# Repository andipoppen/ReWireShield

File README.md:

# ReWireShield
An Arduino compatible shield for rewiring D0-D13 and A0-A5

Exporting to SeedStudio format see:
http://support.seeedstudio.com/knowledgebase/articles/612798-export-pcb-gerber-from-cam

A gerber file viewer can be found here:
http://gerbv.geda-project.org/

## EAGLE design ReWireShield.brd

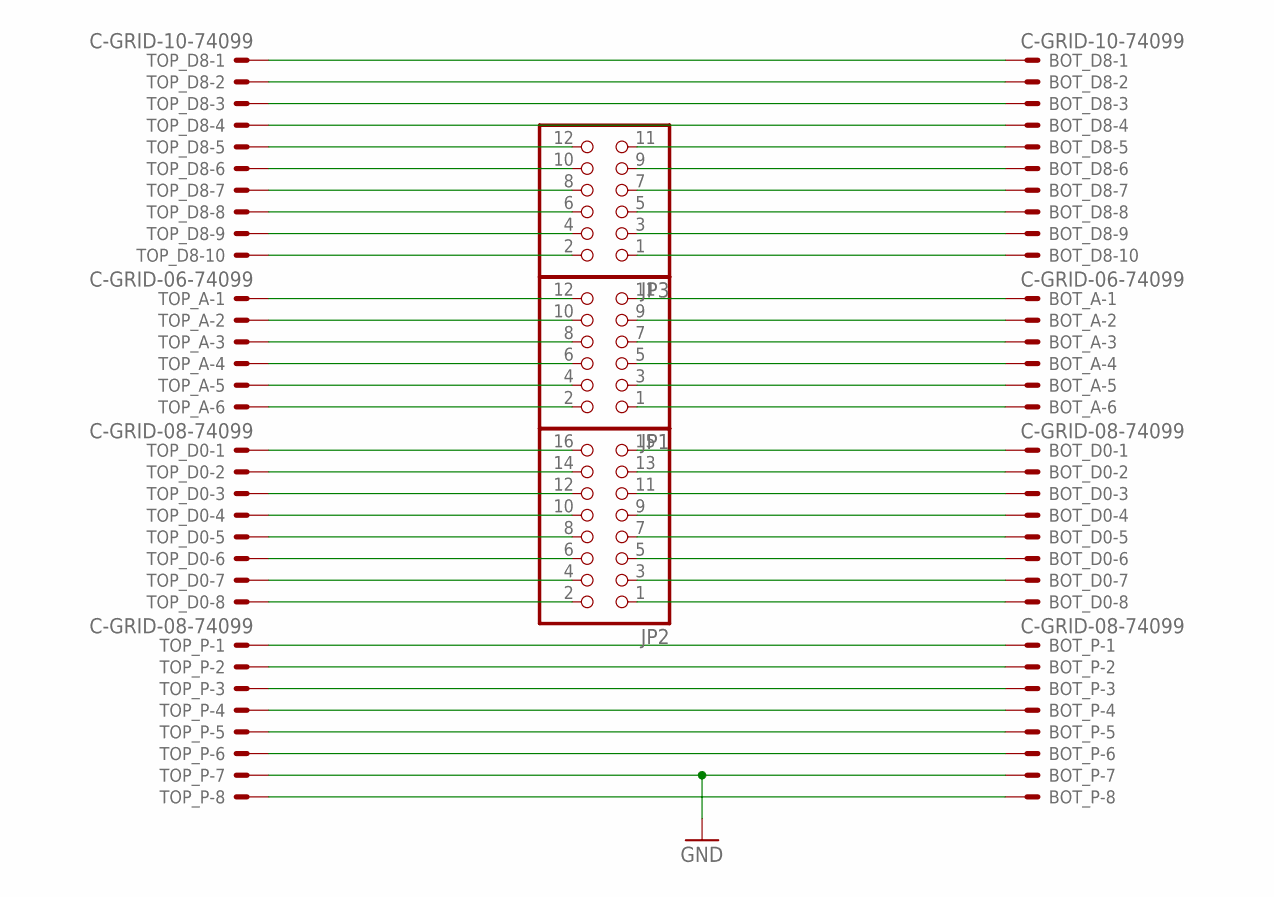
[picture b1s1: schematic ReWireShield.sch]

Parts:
BOT_A: C-GRID-06-74099; 74099-06
BOT_D0: C-GRID-08-74099; 74099-08
BOT_D8: C-GRID-10-74099; 74099-10
BOT_P: C-GRID-08-74099; 74099-08
JP1, JP3: PINHD-2X6/90; 2X06/90
JP2: PINHD-2X8/90; 2X08/90
TOP_A: C-GRID-06-74099; 74099-06
TOP_D0: C-GRID-08-74099; 74099-08
TOP_D8: C-GRID-10-74099; 74099-10
TOP_P: C-GRID-08-74099; 74099-08

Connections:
GND: BOT_P.7, TOP_P.7
unnamed: BOT_P.8, TOP_P.8
unnamed: JP3.2, TOP_D8.10
unnamed: BOT_P.6, TOP_P.6
unnamed: JP3.4, TOP_D8.9
unnamed: BOT_P.4, TOP_P.4
unnamed: BOT_P.3, TOP_P.3
unnamed: BOT_P.2, TOP_P.2
unnamed: BOT_P.1, TOP_P.1
unnamed: JP3.6, TOP_D8.8
unnamed: JP3.8, TOP_D8.7
unnamed: JP3.10, TOP_D8.6
unnamed: JP3.12, TOP_D8.5
unnamed: BOT_D8.10, JP3.1
unnamed: BOT_D8.9, JP3.3
unnamed: JP2.16, TOP_D0.1
unnamed: JP2.14, TOP_D0.2
unnamed: JP1.12, TOP_A.1
unnamed: BOT_D8.8, JP3.5
unnamed: BOT_D0.1, JP2.15
unnamed: BOT_D0.2, JP2.13
unnamed: BOT_D0.3, JP2.11
unnamed: BOT_D0.4, JP2.9
unnamed: BOT_D0.5, JP2.7
unnamed: BOT_D0.6, JP2.5
unnamed: BOT_D0.7, JP2.3
unnamed: BOT_D0.8, JP2.1
unnamed: BOT_A.1, JP1.11
unnamed: BOT_A.2, JP1.9
unnamed: BOT_A.3, JP1.7
unnamed: BOT_A.4, JP1.5
unnamed: BOT_A.5, JP1.3
unnamed: BOT_A.6, JP1.1
unnamed: JP2.12, TOP_D0.3
unnamed: JP2.10, TOP_D0.4
unnamed: JP2.8, TOP_D0.5
unnamed: JP2.6, TOP_D0.6
unnamed: JP2.4, TOP_D0.7
unnamed: JP2.2, TOP_D0.8
unnamed: JP1.10, TOP_A.2
unnamed: JP1.8, TOP_A.3
unnamed: JP1.6, TOP_A.4
unnamed: JP1.4, TOP_A.5
unnamed: JP1.2, TOP_A.6
unnamed: BOT_D8.7, JP3.7
unnamed: BOT_D8.6, JP3.9
unnamed: BOT_D8.5, JP3.11
unnamed: BOT_D8.4, TOP_D8.4
unnamed: BOT_D8.3, TOP_D8.3
unnamed: BOT_P.5, TOP_P.5
unnamed: BOT_D8.2, TOP_D8.2
unnamed: BOT_D8.1, TOP_D8.1

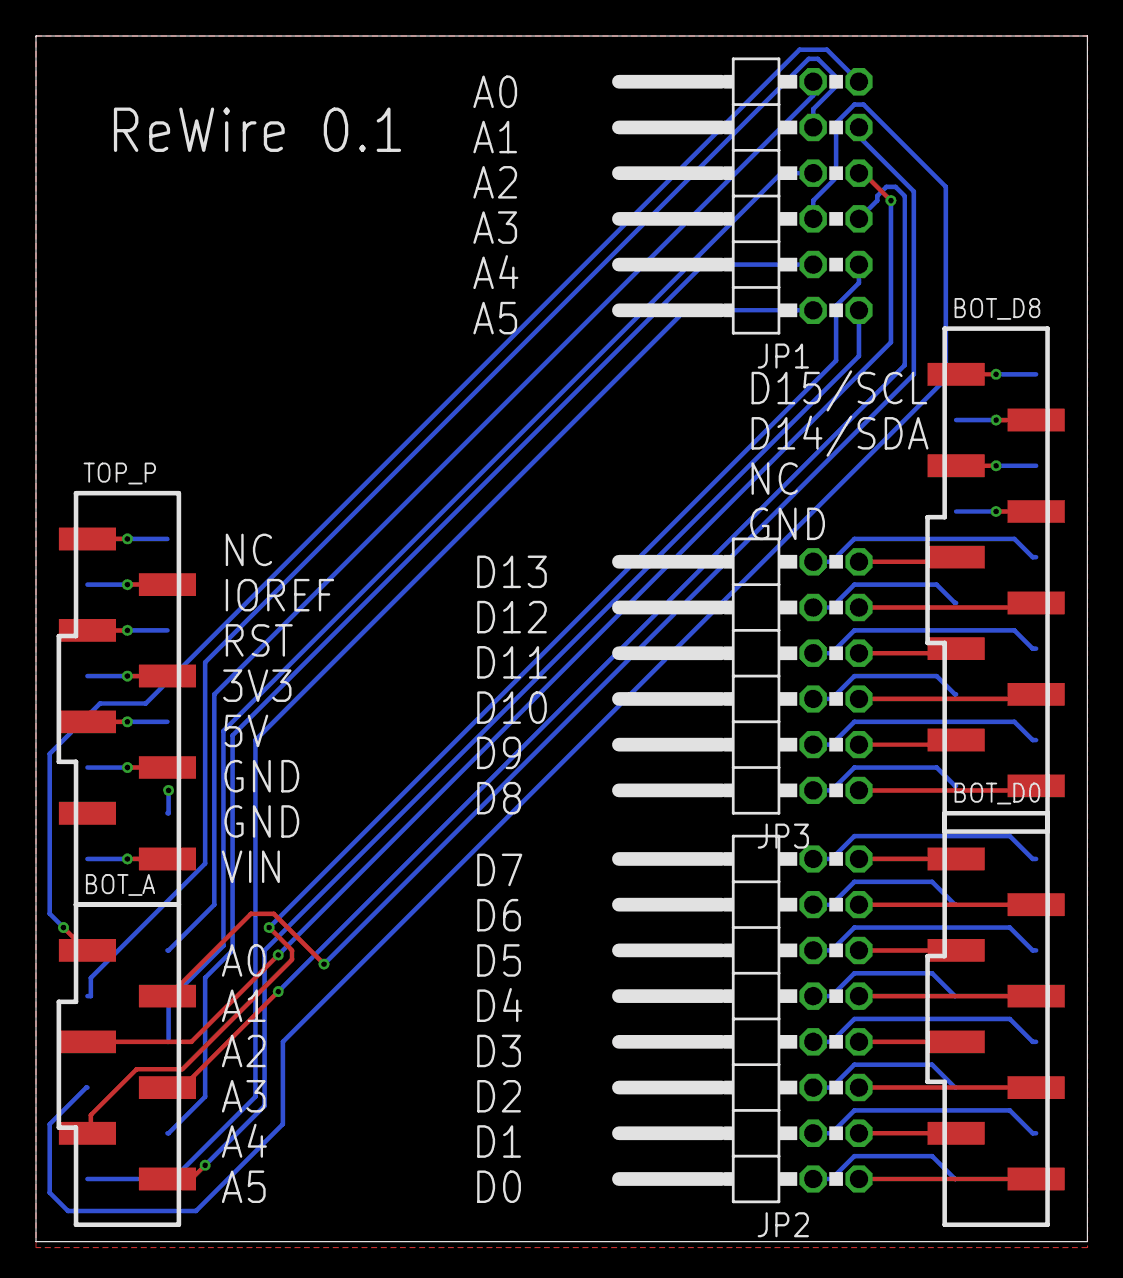
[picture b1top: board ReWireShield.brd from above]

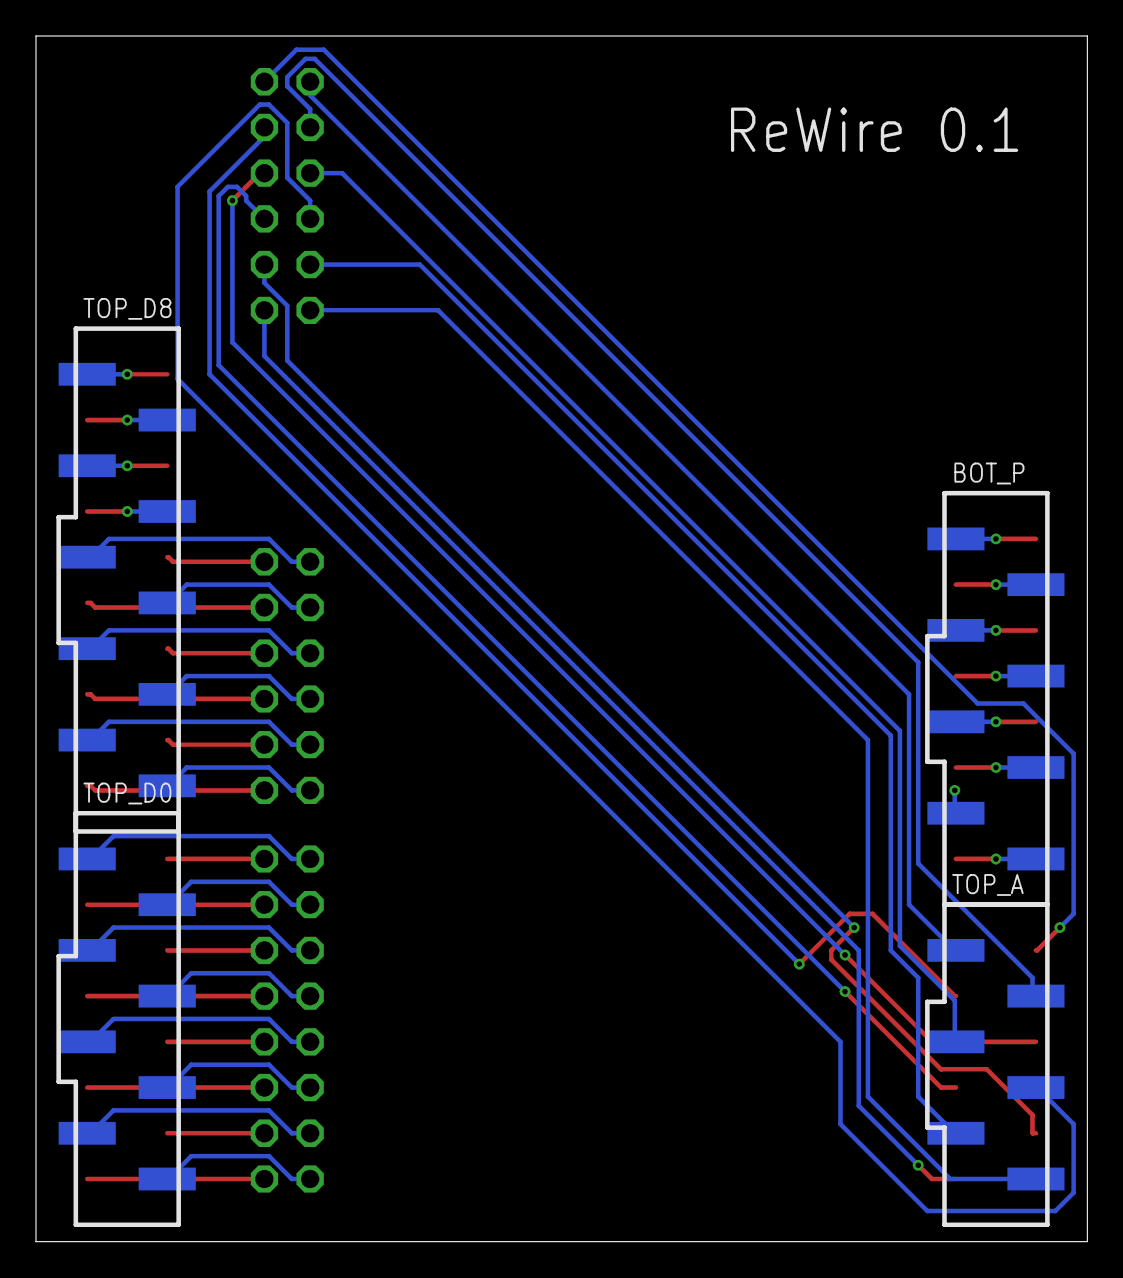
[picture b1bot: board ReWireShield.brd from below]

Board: 4 copper layers, 58.4 x 67.0 mm, 11 parts (4 on the bottom side), 52 nets.
